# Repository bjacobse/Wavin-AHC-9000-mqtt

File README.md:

PCB layout in Kicad, based from this work: https://github.com/dkjonas/Wavin-AHC-9000-mqtt

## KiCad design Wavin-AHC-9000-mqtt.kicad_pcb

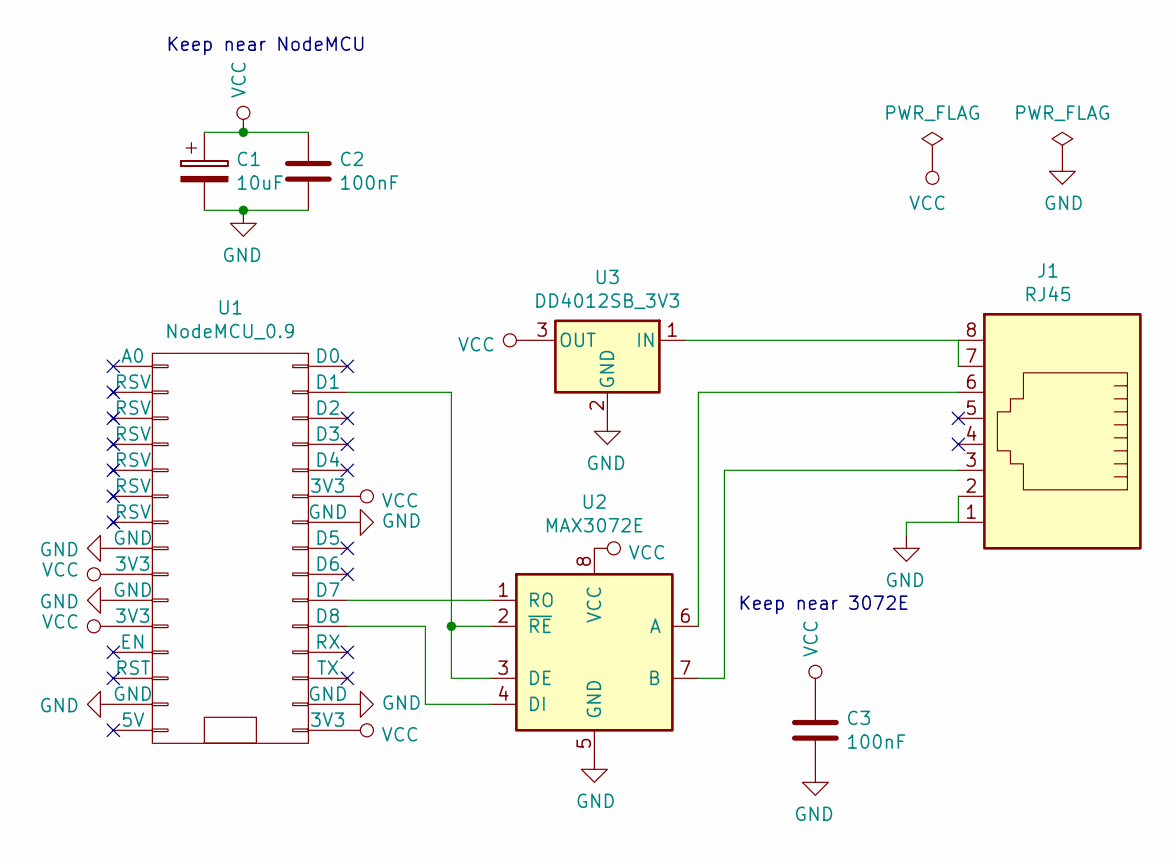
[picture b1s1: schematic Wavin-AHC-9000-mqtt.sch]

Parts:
C1: 10uF; CP_Radial_D10.0mm_P3.50mm
C2, C3: 100nF; C_1206_3216Metric_Pad1.42x1.75mm_HandSolder
J1: RJ45; RJ45_Amphenol_54602-x08_Horizontal
U1: NodeMCU_0.9
U2: MAX3072E; SOIC-8_3.9x4.9mm_P1.27mm
U3: DD4012SB_3V3; Converter_DCDC_RECOM_R-78HB-0.5_THT

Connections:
GND: C1.2, C2.2, C3.2, J1.1, J1.2, U1.8 (GND), U1.10 (GND), U1.14 (GND), U1.17 (GND), U1.24 (GND), U2.5 (GND), U3.2 (GND)
unnamed: J1.3, U2.7 (B)
unnamed: J1.6, U2.6 (A)
unnamed: J1.7, J1.8, U3.1 (IN)
unnamed: U1.20 (D8), U2.4 (DI)
unnamed: U1.21 (D7), U2.1 (RO)
unnamed: U1.29 (D1), U2.2 (~RE~), U2.3 (DE)
VCC: C1.1, C2.1, C3.1, U1.9 (3V3), U1.11 (3V3), U1.16 (3V3), U1.25 (3V3), U2.8 (VCC), U3.3 (OUT)

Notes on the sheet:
Keep near NodeMCU
Keep near 3072E

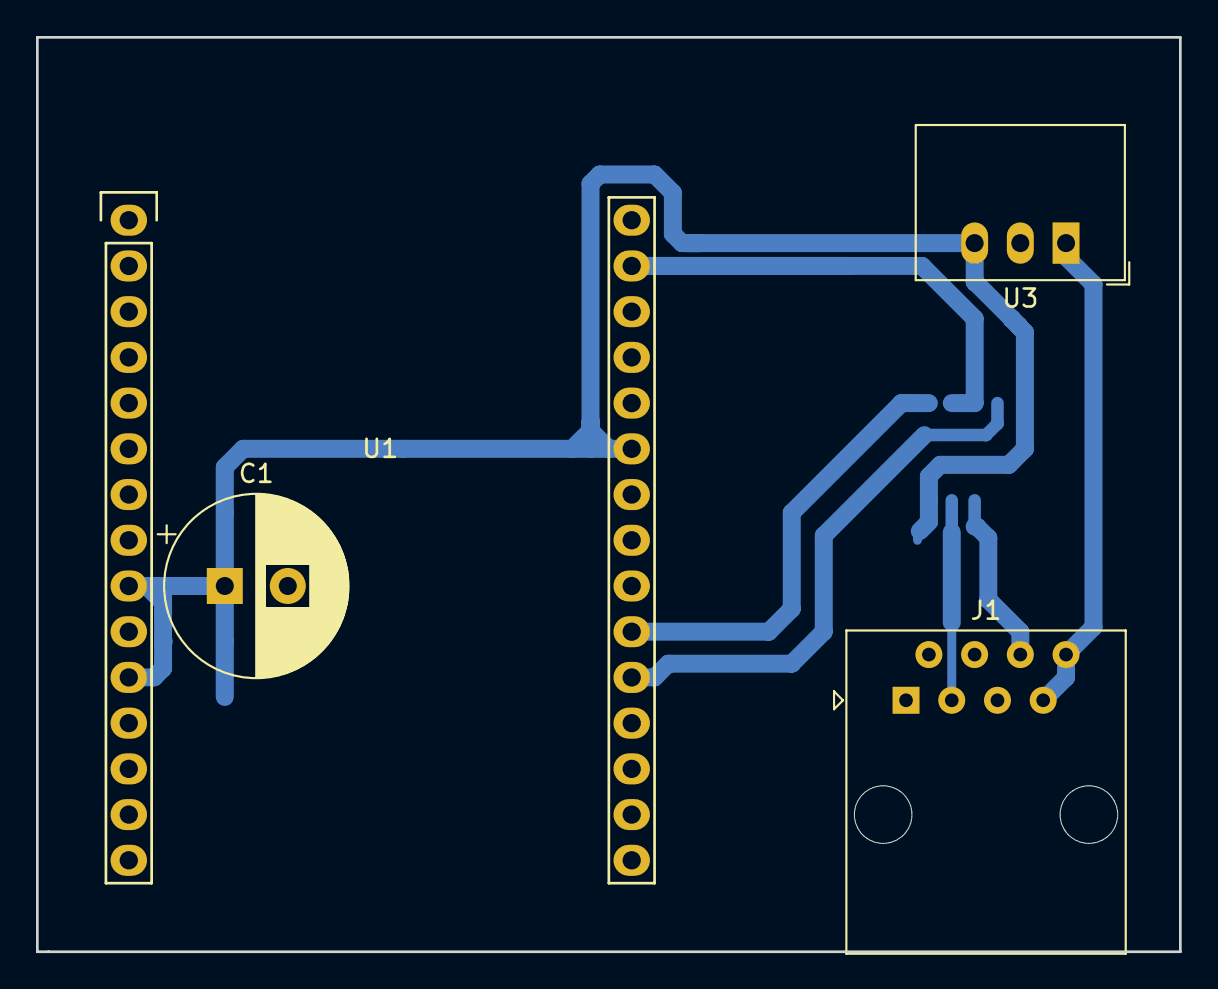
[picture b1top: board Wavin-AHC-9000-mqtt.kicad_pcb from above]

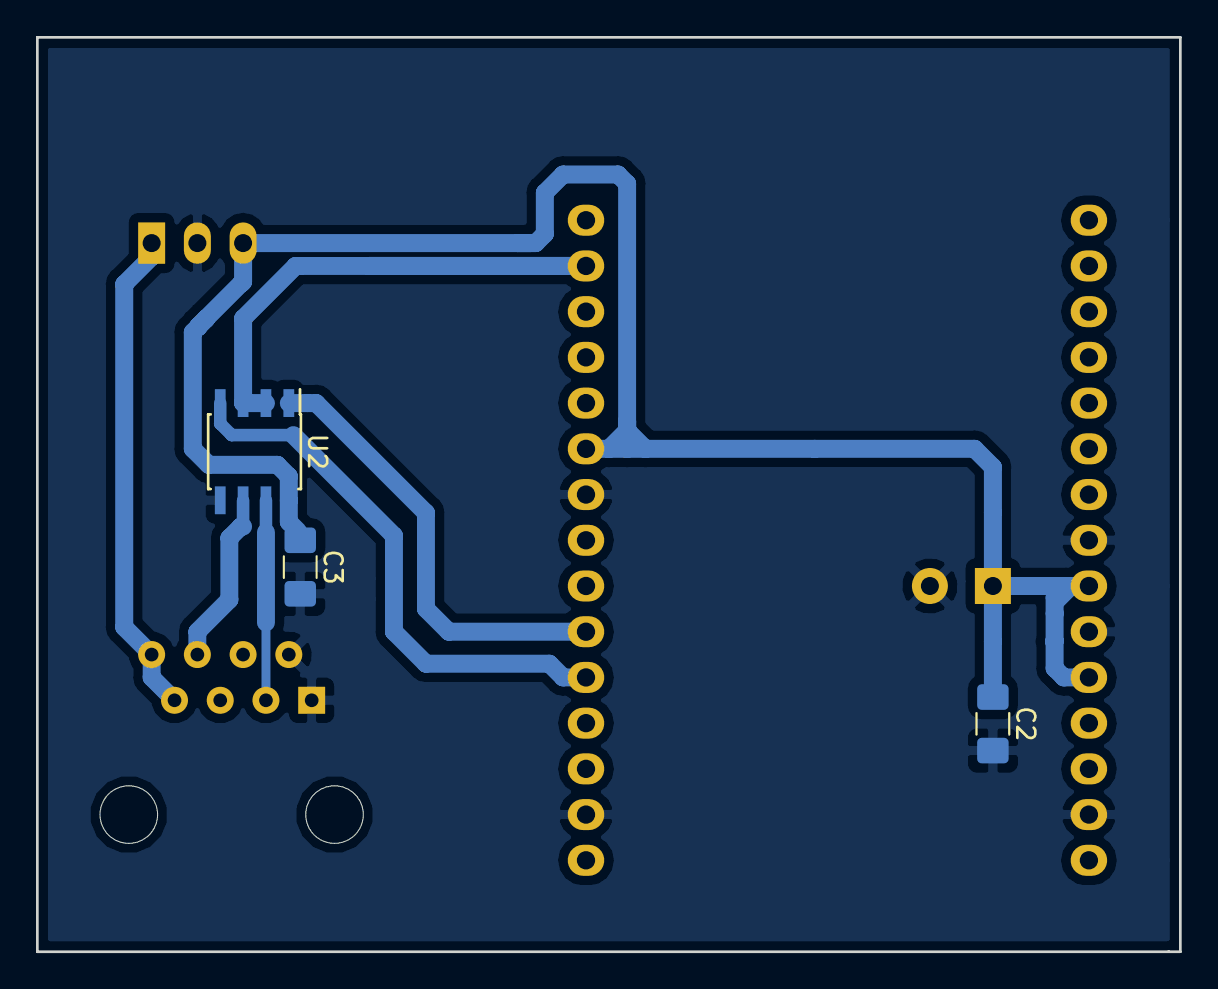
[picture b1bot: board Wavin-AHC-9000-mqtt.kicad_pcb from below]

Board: 2 copper layers, 63.5 x 50.8 mm, 7 parts (3 on the bottom side), 8 nets.
